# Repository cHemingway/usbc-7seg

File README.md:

## USB-C Seven Seg
A USB-C controlled seven segment display, to try out some really tiny SMD 7 seg displays

Designed to be assembled by JLCPCB, using basic parts where possible

Uses a WCH [CH32V203 micro](https://github.com/openwch/ch32v20x) as its small, cheap, has USB 

Credit to Adafruit for the idea of hiding the programming pads on the other side of the USB-C connector

### TODO
- Work out why JLCPCB assembly is so pricy. Maybe this needs to be single sided?
- Check footprint for USB-C connector
- Maybe tidy up the routing, its quite vibe/push-n-shove currently
- Order Rev1 and bring up
- Think of firmware API. USB-CDC, `2.0 <enter>` seems good for now
- Write the firmware

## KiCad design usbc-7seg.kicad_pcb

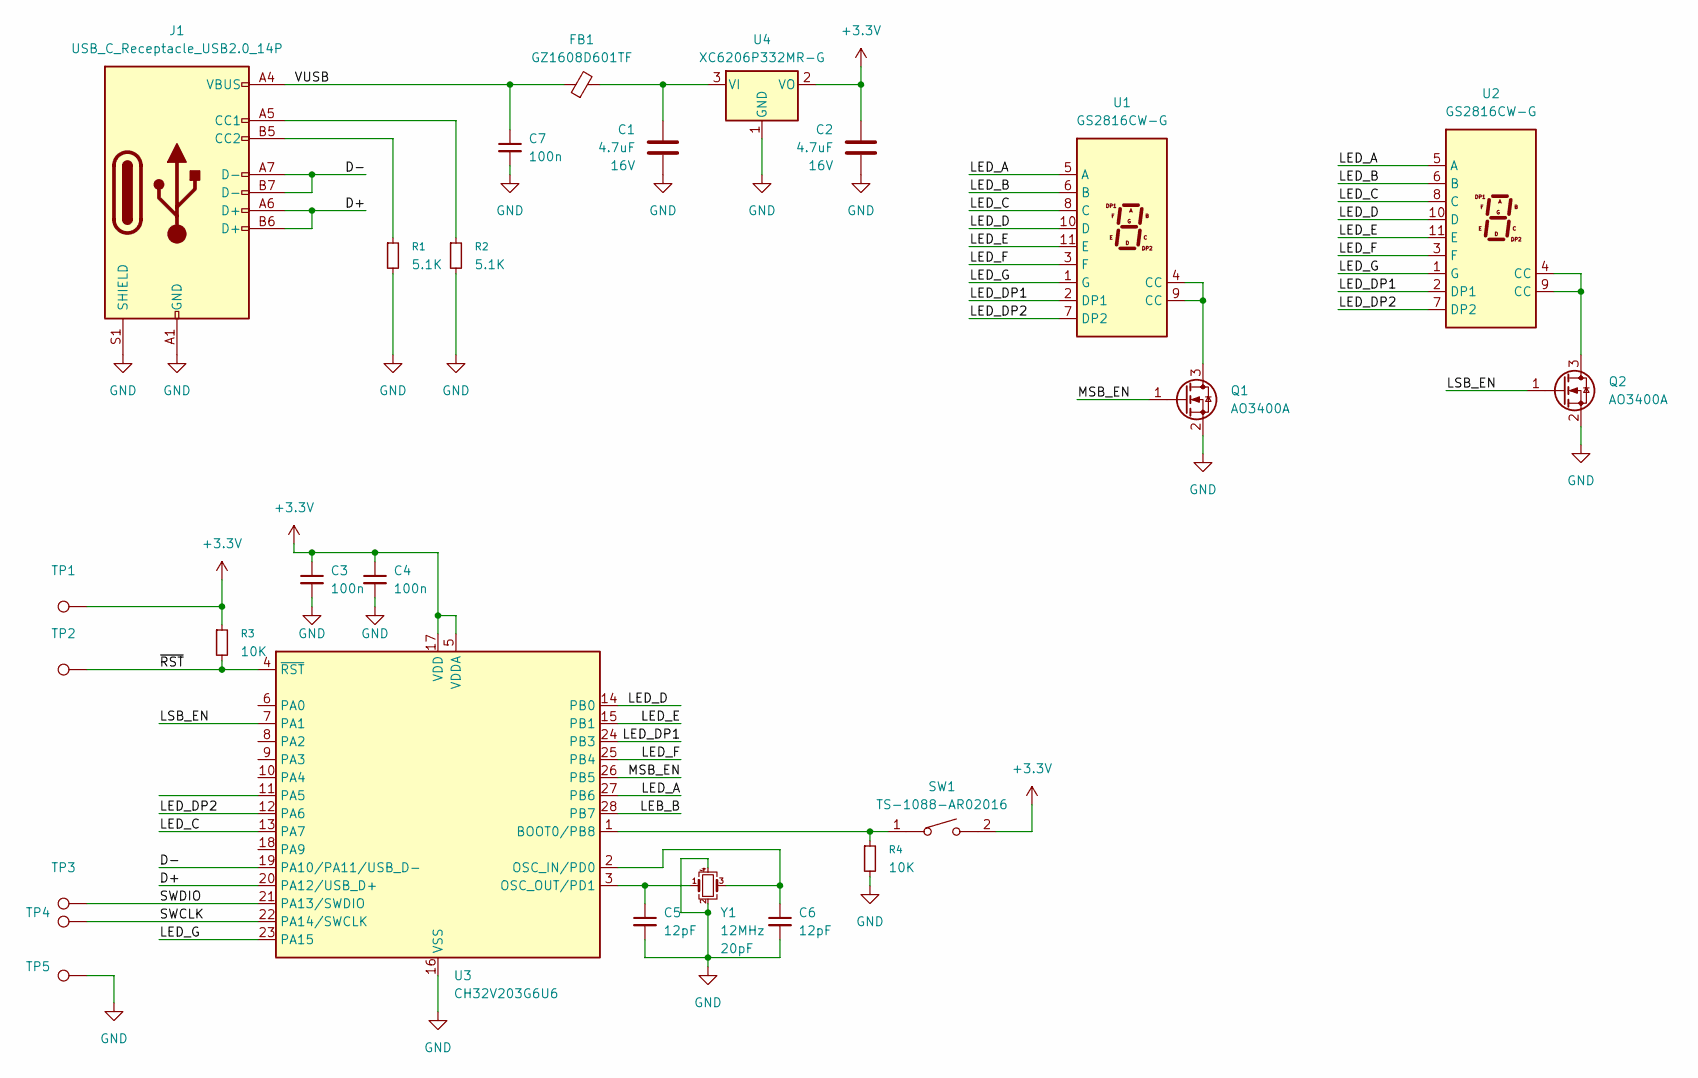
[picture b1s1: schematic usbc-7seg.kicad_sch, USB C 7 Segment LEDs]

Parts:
C1, C2: 4.7uF; C_0603_1608Metric; Voltage 16V; LCSC PN C19666
C3, C4, C7: 100n; C_0402_1005Metric; LCSC PN C1525
C5, C6: 12pF; C_0402_1005Metric; LCSC PN C1547
FB1: GZ1608D601TF; L_0603_1608Metric; LCSC PN C1002
J1: USB_C_Receptacle_USB2.0_14P; USB_C_Receptacle_HCTL_HC-TYPE-C-16P-01A
Q1, Q2: AO3400A; SOT-23; LCSC PN C20917
R1, R2: 5.1K; R_0402_1005Metric; LCSC PN C25905
R3, R4: 10K; R_0402_1005Metric; LCSC PN C25744
SW1: TS-1088-AR02016; SW-SMD_L3.9-W3.0-P4.45; LCSC PN C720477
TP1, TP2, TP3, TP4, TP5: TestPoint_Pad_D1.5mm
U1, U2: GS2816CW-G; GS2816ACX-X; LCSC PN C22462653
U3: CH32V203G6U6; WQFN-28-1EP_4x4mm_P0.4mm_EP2.7x2.7mm; LCSC PN C5142280
U4: XC6206P332MR-G; SOT-23-3; LCSC PN C5446
Y1: 12MHz; Crystal_SMD_3225-4Pin_3.2x2.5mm; LCSC PN C9002

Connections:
+3.3V: C2.1, C3.1, C4.1, R3.1, SW1.2, TP1.1, U3.5 (VDDA), U3.17 (VDD), U4.2 (VO)
/D+: J1.A6 (D+), J1.B6 (D+), U3.20 (PA12/USB_D+)
/D-: J1.A7 (D-), J1.B7 (D-), U3.19 (PA10/PA11/USB_D-)
/LEB_B: U3.28 (PB7)
/LED_A: U1.5 (A), U2.5 (A), U3.27 (PB6)
/LED_B: U1.6 (B), U2.6 (B)
/LED_C: U1.8 (C), U2.8 (C), U3.13 (PA7)
/LED_D: U1.10 (D), U2.10 (D), U3.14 (PB0)
/LED_DP1: U1.2 (DP1), U2.2 (DP1), U3.24 (PB3)
/LED_DP2: U1.7 (DP2), U2.7 (DP2), U3.12 (PA6)
/LED_E: U1.11 (E), U2.11 (E), U3.15 (PB1)
/LED_F: U1.3 (F), U2.3 (F), U3.25 (PB4)
/LED_G: U1.1 (G), U2.1 (G), U3.23 (PA15)
/LSB_EN: Q2.1 (G), U3.7 (PA1)
/MSB_EN: Q1.1 (G), U3.26 (PB5)
/SWCLK: TP4.1, U3.22 (PA14/SWCLK)
/SWDIO: TP3.1, U3.21 (PA13/SWDIO)
/VUSB: C7.1, FB1.1, J1.A4 (VBUS), J1.A9 (VBUS), J1.B4 (VBUS), J1.B9 (VBUS)
/~RST: R3.2, TP2.1, U3.4 (~RST)
GND: C1.2, C2.2, C3.2, C4.2, C5.2, C6.2, C7.2, J1.A1 (GND), J1.A12 (GND), J1.B1 (GND), J1.B12 (GND), J1.S1 (SHIELD), Q1.2 (S), Q2.2 (S), R1.2, R2.2, R4.2, TP5.1, U3.16 (VSS), U3.29 (VSS), U4.1 (GND), Y1.2, Y1.4
unnamed: J1.A5 (CC1), R2.1
unnamed: J1.B5 (CC2), R1.1
unnamed: Q1.3 (D), U1.4 (CC), U1.9 (CC)
unnamed: Q2.3 (D), U2.4 (CC), U2.9 (CC)
unnamed: R4.1, SW1.1, U3.1 (BOOT0/PB8)
unnamed: C6.1, U3.2 (OSC_IN/PD0), Y1.3
unnamed: C5.1, U3.3 (OSC_OUT/PD1), Y1.1
unnamed: C1.1, FB1.2, U4.3 (VI)

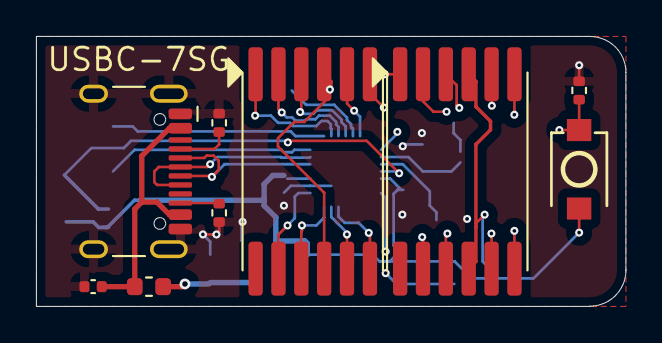
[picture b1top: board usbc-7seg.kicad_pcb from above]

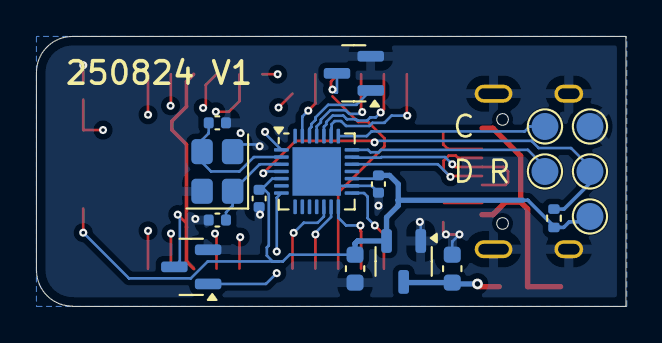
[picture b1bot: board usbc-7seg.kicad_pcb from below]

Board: 4 copper layers, 32.8 x 15.0 mm, 26 parts (17 on the bottom side), 27 nets.

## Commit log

2025-08-23 Initial commit, draft schematic + floorplan
2025-08-23 Some routing, setup board stackup properly
2025-08-24 Routing complete, DRC todo
2025-08-24 Passing DRC
2025-08-24 Add README
2025-08-24 Fix USB-C CC resistors
2025-08-24 First gerber export
2025-08-24 Change to use Fabrication Toolkit for export
2025-08-24 Add JLCPCB part numbers for all parts
